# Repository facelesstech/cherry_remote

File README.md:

# cherry_remote
cherry_remote

Blog post - https://facelesstech.wordpress.com/2019/12/31/cherry-remote/
Youtube - https://youtu.be/F_yzItT-9dE

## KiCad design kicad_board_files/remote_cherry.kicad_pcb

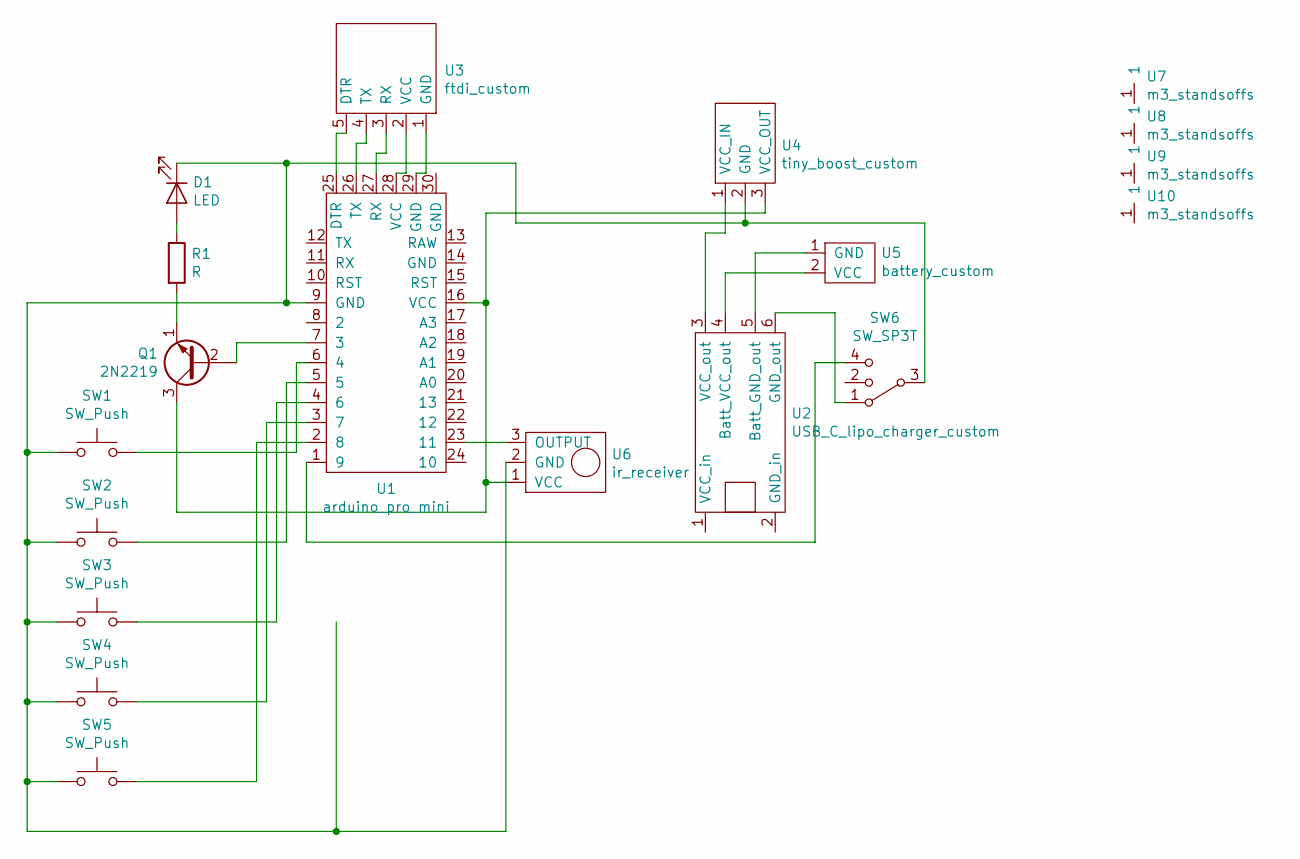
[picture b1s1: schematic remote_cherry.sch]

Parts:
D1: LED; through_hole_led
Q1: 2N2219; 2n2222
R1: R; R_1206_3216Metric
SW1, SW2, SW3, SW4, SW5: SW_Push; SW_Cherry_MX1A_1.00u_PCB
SW6: SW_SP3T; 3_way_switch
U1: arduino_pro_mini; arduino_pro_mini_SMD
U2: USB_C_lipo_charger_custom; USB_C_SMD_lipo_charger_custom
U3: ftdi_custom; gx-12_5pin
U4: tiny_boost_custom; Tiny_boost_orange
U5: battery_custom; jst_2pin_right_angle
U6: ir_receiver
U7, U8, U9, U10: m3_standsoffs; m3_hole_custom

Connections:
unnamed: D1.1 (K), SW1.1, SW2.1, SW3.1, SW4.1, SW5.1, SW6.3, U1.9 (GND), U4.2 (GND), U6.2 (GND)
unnamed: D1.2 (A), R1.1
unnamed: Q1.1 (E), R1.2
unnamed: Q1.2 (B), U1.7 (3)
unnamed: Q1.3 (C), U1.16 (VCC), U4.3 (VCC_OUT), U6.1 (VCC)
unnamed: SW1.2, U1.6 (4)
unnamed: SW2.2, U1.5
unnamed: SW3.2, U1.4 (6)
unnamed: SW4.2, U1.3 (7)
unnamed: SW5.2, U1.2 (8)
unnamed: SW6.1, U2.6 (GND_out)
unnamed: SW6.4, U1.1 (9)
unnamed: U1.23 (11), U6.3 (OUTPUT)
unnamed: U1.25 (DTR), U3.5 (DTR)
unnamed: U1.26 (TX), U3.4 (TX)
unnamed: U1.27 (RX), U3.3 (RX)
unnamed: U1.28 (VCC), U3.2 (VCC)
unnamed: U1.29 (GND), U3.1 (GND)
unnamed: U2.3 (VCC_out), U4.1 (VCC_IN)
unnamed: U2.4 (Batt_VCC_out), U5.2 (VCC)
unnamed: U2.5 (Batt_GND_out), U5.1 (GND)

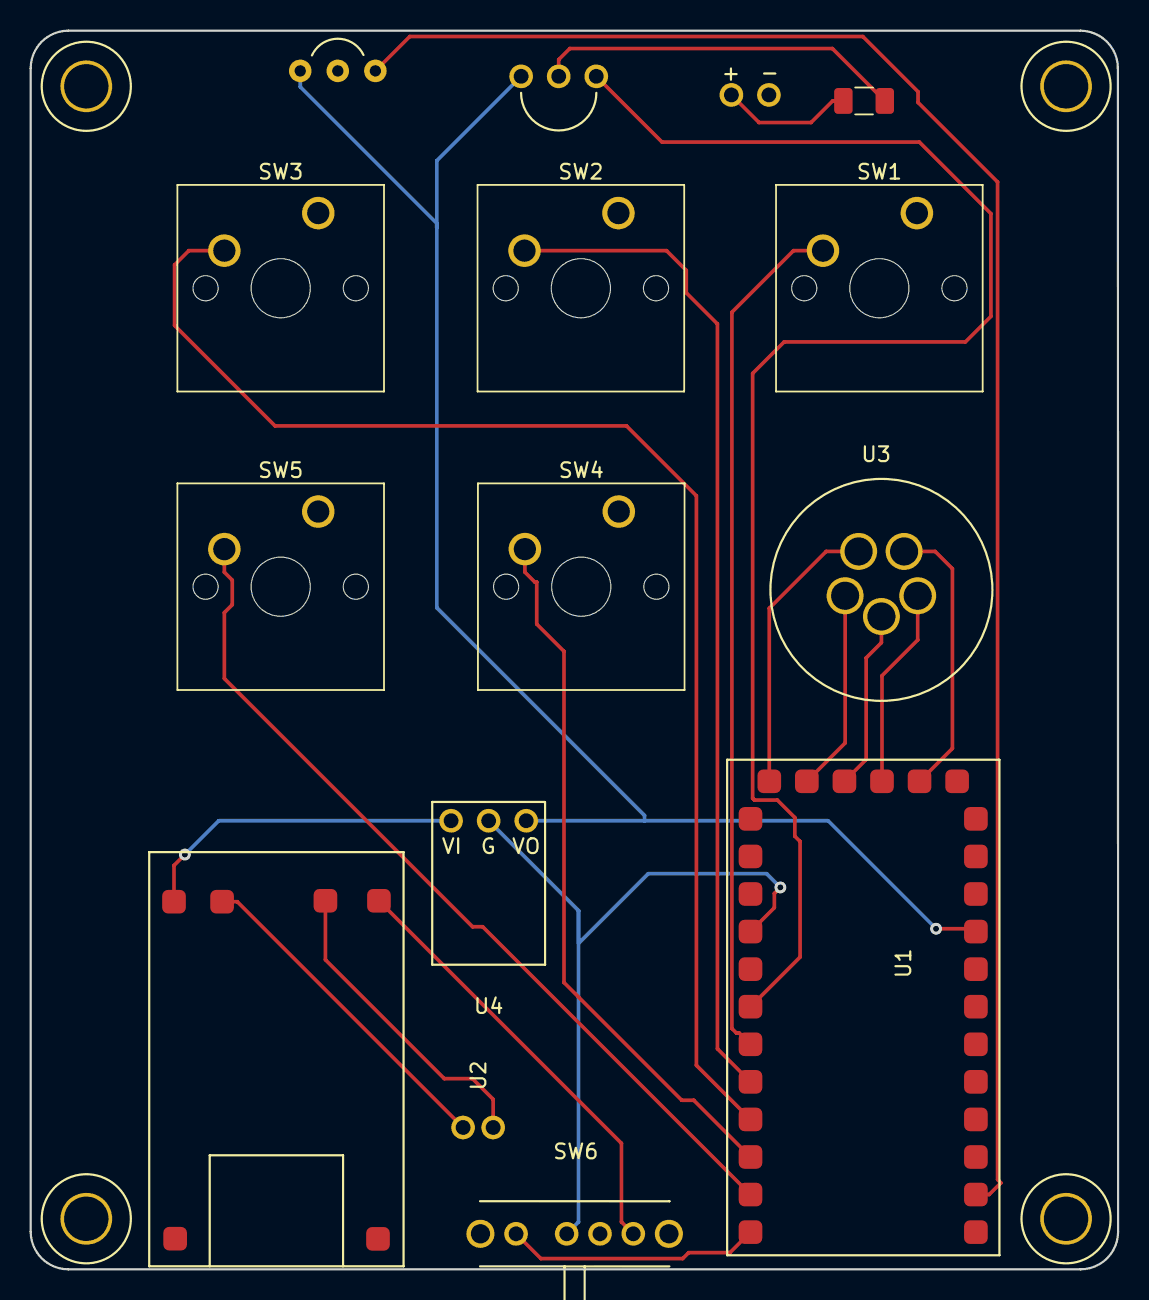
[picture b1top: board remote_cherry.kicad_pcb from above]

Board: 2 copper layers, 73.5 x 83.7 mm, 19 parts (1 on the bottom side), 21 nets.

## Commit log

2019-12-09 3d printing files
2019-12-09 arduino code
2019-12-09 kicad board files
2019-12-15 added key cap files
2019-12-15 added key cap stl files
2020-02-27 added links to readme
2023-08-05 moved folder
2023-08-05 added a new version of the firmware that works with the latest IRremote library
2023-08-05 added new 3d print files
